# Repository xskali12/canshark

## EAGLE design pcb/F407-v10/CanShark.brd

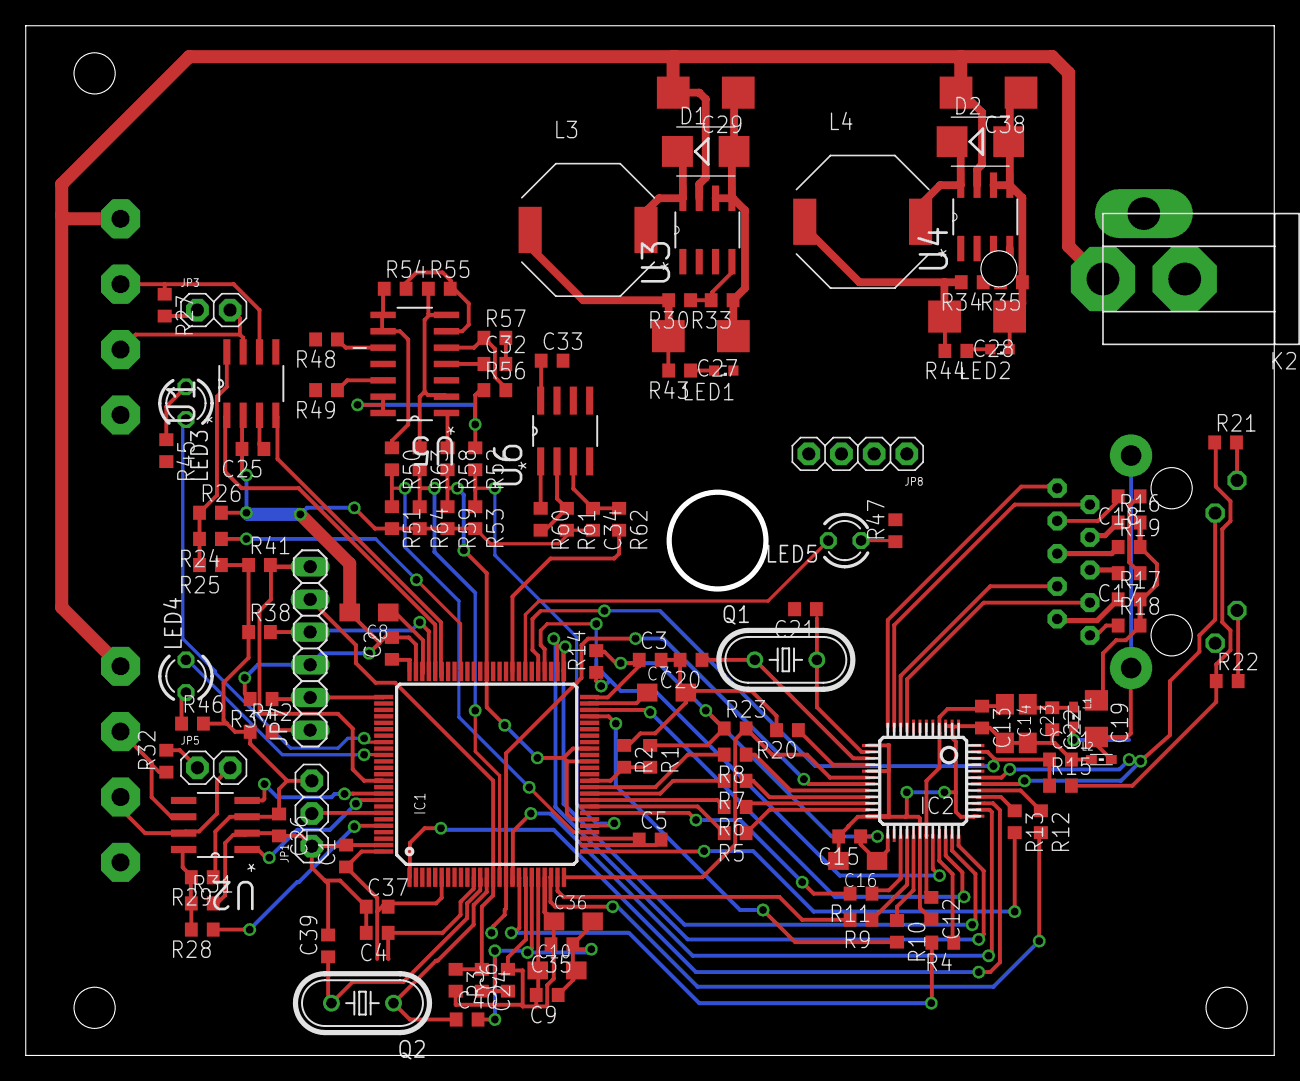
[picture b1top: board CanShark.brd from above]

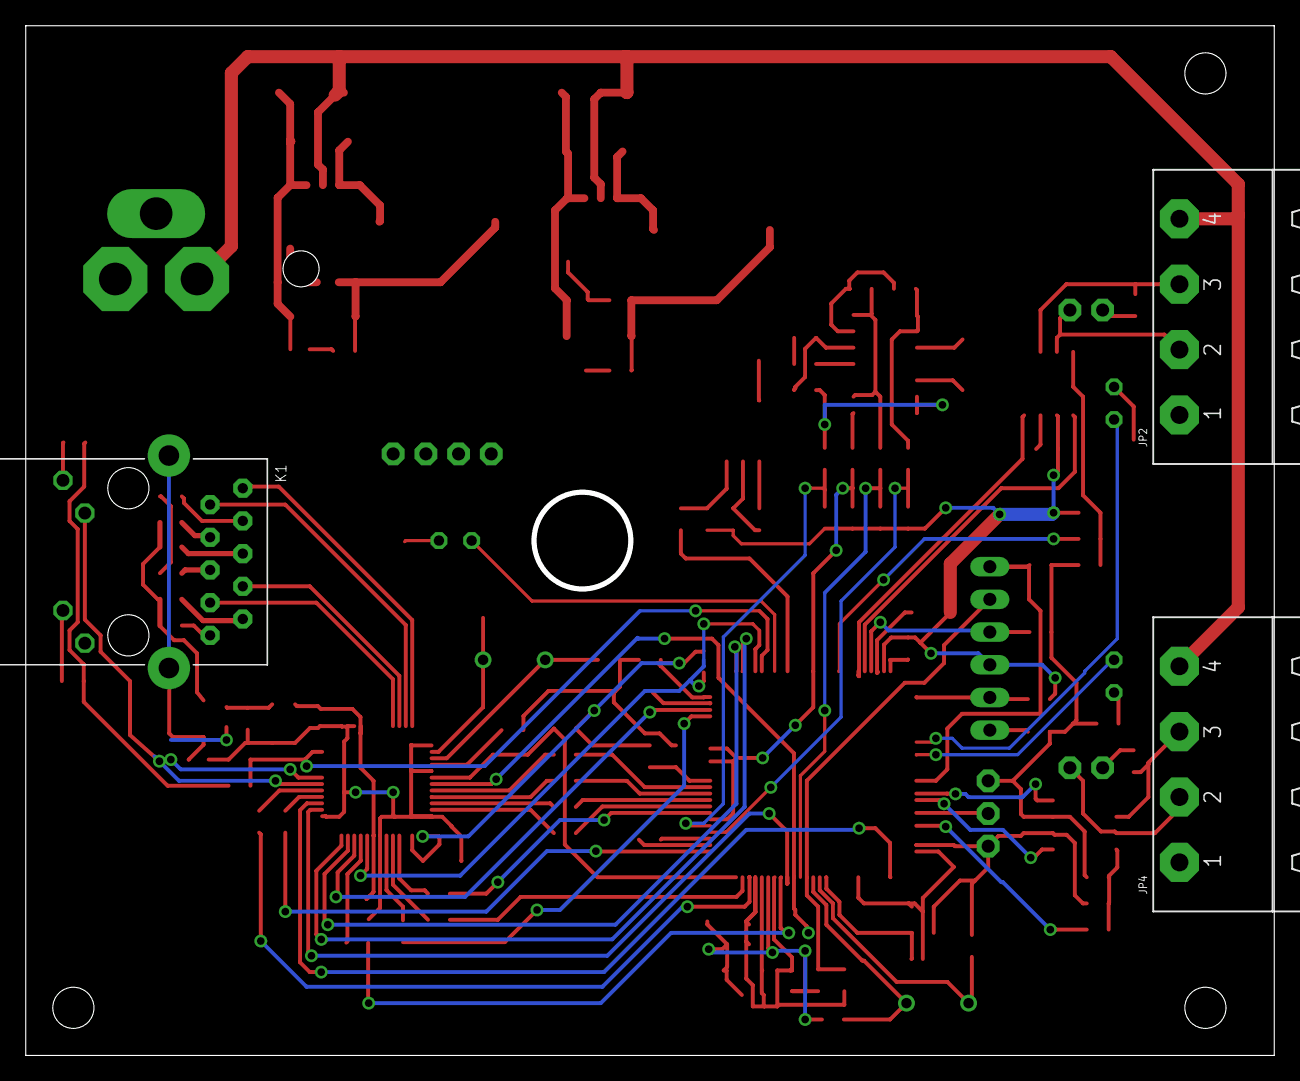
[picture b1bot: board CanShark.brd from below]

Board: 2 copper layers, 97.0 x 80.0 mm, 129 parts (3 on the bottom side), 110 nets.

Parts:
C1, C2, C3, C4, C5, C6, C11, C12, C13, C15, C17, C18, C22, C24, C25, C26, C32, C33, C34, C37: 100nF; SMD0603
C7, C8, C14, C16: 2,2uF; SMC_A
C9, C35: 10nF; SMD0603
C10, C36: 1uF; SMC_A
C19: 1000pF/2kV; SMD1206
C20, C21, C39, C40: 22p; SMD0603
C23: 22uF; SMC_A
C27, C28, C29, C38: C/6032-28R
D1, D2: SMB
IC1: STM32F407V; LQFP100
IC2: KSZ8051MLL; LQFP48
JP1: 1X03_254
JP2, JP4: 1X04_508_H
JP3, JP5: 1X02_254
JP7: 1X06
JP8: 1X04_254
K1: RJ45_TRAFO
K2: JACK_POWER_2,1; J_P_2,1
L1, L2: 0603
L3, L4: WE-TPC_1028/1038
LED1, LED2: SML0603
LED3, LED4, LED5: TLLG4400; LED3MM
Q1, Q2: HC49U-V
R1, R2, R24, R25, R26, R28, R29, R31, R42, R48, R49: 0R; R0603
R3, R15, R45, R46, R47, R54, R55, R56, R57: 10k; R0603
R4, R5, R6, R7, R8, R9, R10, R11, R12, R13: 33R; R0603
R14, R21, R22: 4,7k; R0603
R16, R17, R18, R19: 75R; R0603
R20: 6,49k; R0603
R23: 1k; R0603
R27, R32: 120R; R0603
R30: 8,2k; R0603
R33: 1,1k; R0603
R34: 2k; R0603
R35, R43: 1,2k; R0603
R37, R38, R41, R51, R53, R64: 100k; R0603
R44: 330R; R0603
R50: 200K; R0603
R52, R58, R59, R63: 200k; R0603
R60: 22k; R0603
R61: 11k; R0603
R62: 300k; R0603
U1, U2: SN65HVD230DR; SOIC127P600X175-8N
U3, U4: LM2594M-ADJ; SOIC127P620X175-8N
U5: TSH24IDT; SOIC127P600X175-14N
U6: MCP602-E/SN; SOIC127P600X175-8N

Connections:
+3V3: C1.1, C2.1, C3.1, C4.1, C6.2, C9.2, C10.+, C15.1, C16.+, C25.1, C26.1, C28.+, C35.2, C36.+, C37.2, IC1.6, IC1.11, IC1.19, IC1.21, IC1.22, IC1.50, IC1.75, IC1.100, IC2.25, JP1.3, JP8.1, L1.2, L4.2, R1.1, R3.2, R14.2, R15.2, R21.1, R22.1, R23.1, R25.1, R29.1, R34.2, R38.1, R41.1, R42.1, R44.2, R45.2, R46.2, R47.2, U1.3, U2.3
ADC_CAN1DIFF: IC1.15, R63.2, R64.1
ADC_CAN1H: IC1.30, R52.2, R53.1
ADC_CAN1L: IC1.29, R50.2, R51.1
ADC_TRIG: IC1.31, IC1.40, IC1.42, IC1.63, R58.2, R59.1
ADC_TRIG_VALUE_PWM: IC1.59, R62.2
CAN1_H: JP2.2, JP3.2, R49.2, U1.7
CAN1_L: JP2.3, R27.1, R48.2, U1.6
CAN1_MODE: IC1.67, R24.1
CAN1_RX: IC1.70, U1.4
CAN1_TX: IC1.71, U1.1
CAN2_MODE: IC1.96, R28.1
CAN2_RX: IC1.91, U2.4
CAN2_TX: IC1.92, U2.1
CANL: JP4.3, R32.1, U2.6
ETH_INTRP: IC1.54, IC2.32, R14.1
ETH_MDC: IC1.16, IC2.19
ETH_MDIO: IC1.25, IC2.18, R23.2
ETH_MII_COL: IC1.26, R13.2
ETH_MII_CRS: IC1.23, R12.2
ETH_MII_RXD0: IC1.33, R5.2
ETH_MII_RXD1: IC1.34, R6.2
ETH_MII_RXD2: IC1.35, R7.2
ETH_MII_RXD3: IC1.36, R8.2
ETH_MII_RX_CLK: IC1.24, R9.2
ETH_MII_RX_DV: IC1.32, R11.2
ETH_MII_RX_ER: IC1.47, R10.2
ETH_MII_TXD0: IC1.51, IC2.35
ETH_MII_TXD1: IC1.52, IC2.36
ETH_MII_TXD2: IC1.17, IC2.38
ETH_MII_TXD3: IC1.1, IC2.39
ETH_MII_TX_CLK: IC1.18, R4.2
ETH_MII_TX_EN: IC1.48, IC2.34
ETH_RST: C11.1, IC1.55, IC2.47, R15.1
EXTSUPPLY: C29.+, C38.+, JP2.4, JP4.4, K2.A, U3.7, U4.7
GND: C1.2, C2.2, C3.2, C4.2, C5.2, C6.1, C7.-, C8.-, C9.1, C10.-, C11.2, C12.2, C13.2, C14.-, C15.2, C16.-, C17.1, C18.1, C20.2, C21.2, C22.2, C23.-, C24.2, C25.2, C26.2, C27.-, C28.-, C29.-, C32.2, C33.2, C34.2, C35.1, C36.-, C37.1, C38.-, C39.2, C40.2, D1.A, D2.A, IC1.10, IC1.20, IC1.27, IC1.74, IC1.99, IC2.1, IC2.2, IC2.3, IC2.13, IC2.17, IC2.24, IC2.30, IC2.37, JP1.1, JP2.1, JP4.1, JP7.3, JP8.4, K2.B, L2.1, LED1.C, LED2.C, R2.1, R20.2, R26.2, R31.2, R33.1, R35.1, R37.2, R51.2, R53.2, R57.2, R59.2, R61.2, R64.2, U1.2, U2.2, U3.5, U3.6, U4.5, U4.6, U5.11, U6.4
JTG-TCK/SWCLK: IC1.76, JP7.2, R37.1
JTG-TDO/SWO: IC1.89, JP7.6, R41.2
JTG-TMS/SWDIO: IC1.72, JP7.4, R38.2
LED_CAN1: IC1.83, LED3.K
LED_CAN2: IC1.85, LED4.K
LED_GLOBAL: IC1.57, LED5.K
unnamed: IC1.94, JP1.2
unnamed: C7.+, IC1.49
unnamed: C5.1, IC1.28
unnamed: C8.+, IC1.73
unnamed: JP3.1, R27.2
unnamed: IC1.37, R1.2, R2.2
unnamed: D1.C, L3.1, U3.8
unnamed: C22.1, C23.+, IC2.7, L1.1
unnamed: IC2.33, R4.1
unnamed: R24.2, R25.2, R26.1, U1.8
unnamed: JP4.2, JP5.2, U2.7
unnamed: IC2.28, R9.1
unnamed: R28.2, R29.2, R31.1, U2.8
unnamed: IC2.23, R5.1
unnamed: IC2.22, R6.1
unnamed: IC2.21, R7.1
unnamed: IC2.20, R8.1
unnamed: IC2.29, R10.1
unnamed: IC2.27, R11.1
unnamed: IC2.41, R12.1
unnamed: IC2.40, R13.1
unnamed: JP5.1, R32.2
unnamed: JP7.1, R42.2
unnamed: D2.C, L4.1, U4.8
unnamed: R34.1, R35.2, U4.4
unnamed: R30.1, R33.2, U3.4
unnamed: LED1.A, R43.1
unnamed: C12.1, C13.1, C14.+, IC2.4, IC2.31
unnamed: IC2.9, K1.8
unnamed: IC2.10, K1.7
unnamed: IC2.11, K1.2
unnamed: IC2.12, K1.1
unnamed: K1.4, R16.1
unnamed: K1.9, R17.1
unnamed: K1.10, R18.1
unnamed: K1.5, R19.1
unnamed: C19.1, R16.2, R17.2, R18.2, R19.2
unnamed: C17.2, K1.6
unnamed: C18.2, K1.3
unnamed: C19.2, K1.SH1, K1.SH2, L2.2
unnamed: IC2.16, R20.1
unnamed: IC2.42, K1.K_G
unnamed: IC2.43, K1.K_Y
unnamed: K1.A_Y, R22.2
unnamed: K1.A_G, R21.2
unnamed: LED2.A, R44.1
unnamed: C21.1, IC2.14, Q1.2
unnamed: C20.1, IC2.15, Q1.1
unnamed: LED3.A, R45.1
unnamed: LED4.A, R46.1
unnamed: LED5.A, R47.1
unnamed: R52.1, R56.1, U5.13, U5.14
unnamed: R50.1, R54.1, U5.8, U5.9
unnamed: R49.1, U5.12
unnamed: R48.1, U5.10
unnamed: R55.1, R63.1, U5.2, U5.7
unnamed: R54.2, R55.2, U5.6
unnamed: R56.2, R57.1, U5.5
unnamed: R60.1, U5.3, U6.1
unnamed: R58.1, U5.1
unnamed: R60.2, R61.1, U6.2
unnamed: C34.1, R62.1, U6.3
NRST: C24.1, IC1.14, JP7.5, R3.1
OSC_IN: C39.1, IC1.12, Q2.2
OSC_OUT: C40.1, IC1.13, Q2.1
USART1_RX: IC1.69, JP8.3
USART1_TX: IC1.68, JP8.2
V+: C27.+, C32.1, C33.1, L3.2, R30.2, R43.2, U5.4, U6.8

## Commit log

2013-09-23 Correct the timestamp display.
2013-09-23 [canshark-gui] Add first version of GUI
2013-09-23 [canshark-gui] Add ignored folders
2013-09-23 [sw/canshark-console] Add argument parsing, rewritten to event driven packet capture.
2013-09-23 [sw/canshark-console] Add parameter configuration
2013-09-23 [sw/canshark-gui] Add packet statistics
2013-09-23 [sw/canshark-gui] Add the Canopen cycle log, first version
2013-10-03 [Dissector] Add CanOpen SDO dissection engine
2013-10-04 [Dissector] Properly manage the CAN dissector tree
2013-10-04 [Dissector] Speed-up the dissection of packet data using LUT
2013-10-04 [Dissector] Optimize speed
2013-11-07 Oprava zobrazeni cyklu CAN sbernice ikdyz nejsou zpravy
2013-11-07 Pridan vypocet delky zpravy (bez vsunutych bitu)
2013-11-07 Add cycle log for CAN2
2014-03-22 add schematic of MCU and Ethernet part
2014-03-22 Add schematic for CAN-BUS interface part
2014-04-01 Add power supply
2014-04-06 Add JTAG/SWD and LEDs
2014-04-07 add ADC
2014-04-13 Add debug USART and split power supplies
2014-04-13 Remove .s#x files
2014-04-19 Add board dimension for KM 35
2014-04-27 Add MCU crystal to schematic, change pcb
2014-04-27 Change Board
2014-04-28 design PCB modules
2014-04-30 Rotate groups on board
2014-04-30 remove JTAG connector,
2014-05-01 Change LED, ETH RST and INTRPT pins on processor
2014-05-01 Change debug USART, finish routing
2014-05-02 add GND polygon
2014-05-11 [pcb] change mounting hole position, increase the isolation gap
2014-05-20 Add EM::Blocks project
2014-05-25 [pcb] change texts of PCB
2014-05-25 [fw]Change pinout for CanShark board, add prescaler to main LED toggle

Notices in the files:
parts and their libraries:
Copyright (C) Vlada 2004-2005
